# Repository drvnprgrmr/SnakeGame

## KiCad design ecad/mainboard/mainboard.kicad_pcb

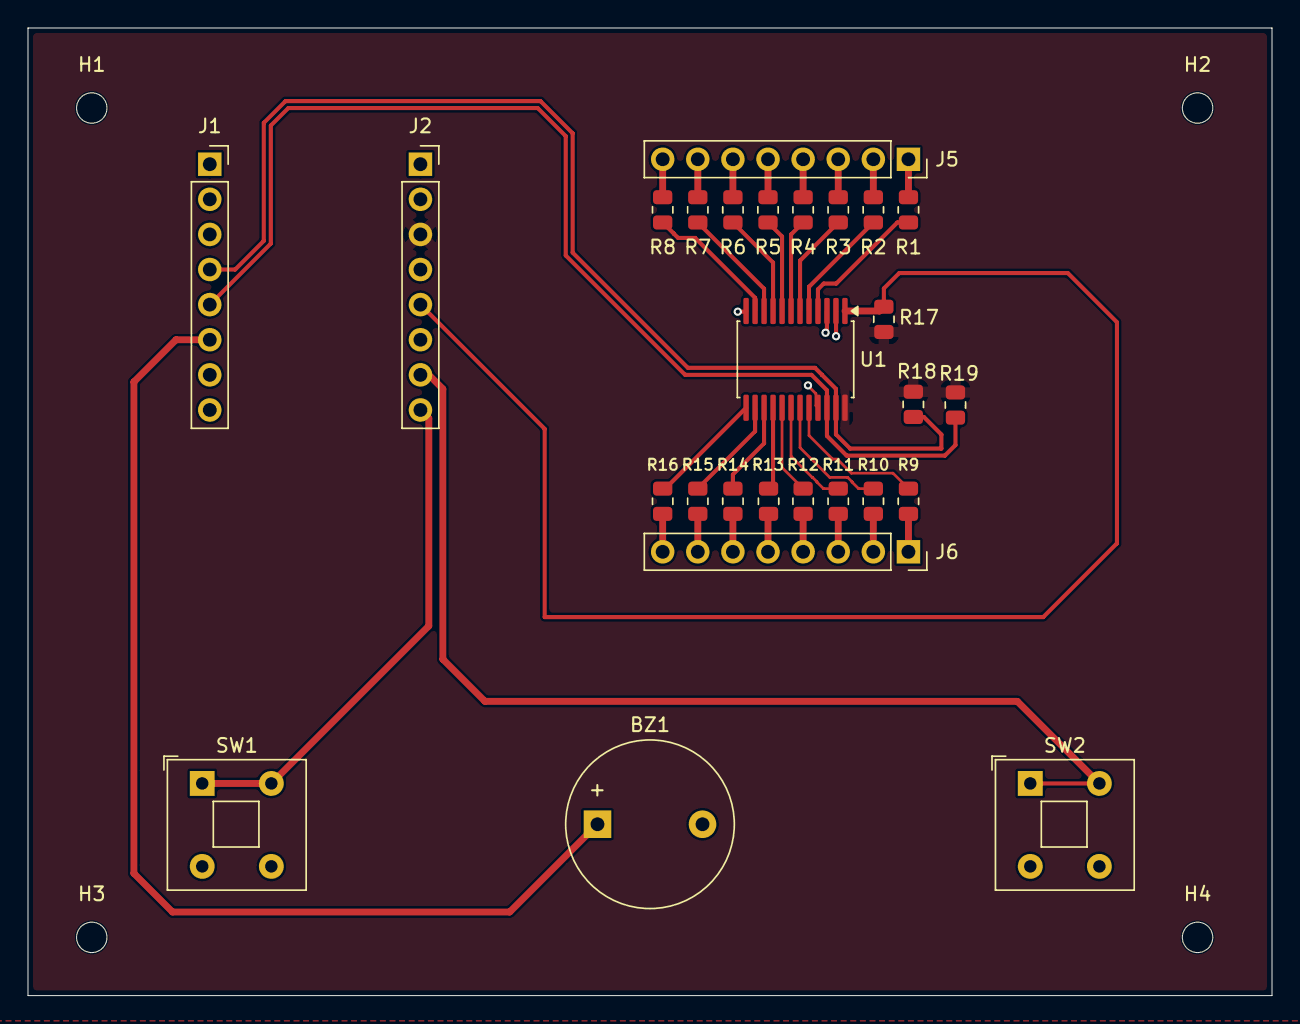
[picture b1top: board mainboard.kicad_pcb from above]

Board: 2 copper layers, 90.0 x 70.0 mm, 31 parts (0 on the bottom side), 40 nets.

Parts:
BZ1: Buzzer; Buzzer_12x9.5RM7.6
H1, H2, H3, H4: MountingHole; MountingHole_2.2mm_M2
J1: ESP32C3 Super Mini Left; PinSocket_1x08_P2.54mm_Vertical
J2: ESP32C3 Super Mini Right; PinSocket_1x08_P2.54mm_Vertical
J5: Dot Matrix Side A; PinSocket_1x08_P2.54mm_Vertical
J6: Dot Matrix Side B; PinSocket_1x08_P2.54mm_Vertical
R1, R2, R3, R4, R5, R6, R7, R8, R9, R10, R11, R12, R13, R14, R15, R16: 150; R_0805_2012Metric
R17: 10k; R_0805_2012Metric
R18, R19: 4.7k; R_0805_2012Metric
SW1: Left Button; SW_Push_2P1T_Toggle_CK_PVA1xxH1xxxxxxV2
SW2: Right Button; SW_Push_2P1T_Toggle_CK_PVA1xxH1xxxxxxV2
U1: PCF8575DBR; SSOP-24_5.3x8.2mm_P0.65mm

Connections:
+3.3V: J2.3, R17.1, R18.1, R19.1, U1.24 (VCC)
/BUZZ: BZ1.1 (+), J1.6
/DM_A1: J5.1, R1.1
/DM_A2: J5.2, R2.1
/DM_A3: J5.3, R3.1
/DM_A4: J5.4, R4.1
/DM_A5: J5.5, R5.1
/DM_A6: J5.6, R6.1
/DM_A7: J5.7, R7.1
/DM_A8: J5.8, R8.1
/DM_B1: J6.1, R9.1
/DM_B2: J6.2, R10.1
/DM_B3: J6.3, R11.1
/DM_B4: J6.4, R12.1
/DM_B5: J6.5, R13.1
/DM_B6: J6.6, R14.1
/DM_B7: J6.7, R15.1
/DM_B8: J6.8, R16.1
/LEFT_BTN: J2.8, SW1.1, SW1.2
/P0: R1.2, U1.4 (P0)
/P1: R2.2, U1.5 (P1)
/P2: R3.2, U1.6 (P2)
/P3: R4.2, U1.7 (P3)
/P4: R5.2, U1.8 (P4)
/P5: R6.2, U1.9 (P5)
/P6: R7.2, U1.10 (P6)
/P7: R8.2, U1.11 (P7)
/P10: R16.2, U1.13 (P10)
/P11: R15.2, U1.14 (P11)
/P12: R14.2, U1.15 (P12)
/P13: R13.2, U1.16 (P13)
/P14: R12.2, U1.17 (P14)
/P15: R11.2, U1.18 (P15)
/P16: R10.2, U1.19 (P16)
/P17: R9.2, U1.20 (P17)
/RIGHT_BTN: J2.7, SW2.1, SW2.2
/SCL: J1.5, R19.2, U1.22 (SCL)
/SDA: J1.4, R18.2, U1.23 (SDA)
/~INT: J2.5, R17.2, U1.1 (~INT)
GND: BZ1.2 (-), J2.2, SW1.3 (K), SW1.4 (A), SW2.3 (K), SW2.4 (A), U1.2 (A1), U1.3 (A2), U1.12 (GND), U1.21 (A0)

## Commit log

2026-04-16 initial commit
    setup esp-idf
2026-04-16 add dot_matrix module for interfacing with the dot matrix
2026-04-16 configure all row and column pins
    add readme and put description of working of the matrix
2026-04-16 add function to display init sequence for testing addressing
2026-04-17 add helper functions for multiplexing
2026-04-17 add license
2026-04-17 last commit with old logic
2026-04-17 load screen not working and watchdog being triggered
2026-04-17 almost fixed loadscreen
2026-04-17 fix display issues by implementing row by row scanning and adding sleep delay in the microseconds
    should be able to get them brighter by using lower LEDs (maybe 810ohms)
2026-04-17 fix load screen
2026-04-18 implement logic for moving snake
2026-04-18 draw snake and update in all 4 directions
2026-04-18 setup wifi softap
2026-04-18 fix logic of snake motion
2026-04-18 working on captive portal with issues
2026-04-19 get captive portal page working and redirecting
    yaato!
2026-04-19 add route for posting data and update web page to send json
2026-04-19 receive the data sent from queue
    really don't know what was wrong before
2026-04-19 get and store values from nvs
2026-04-20 setup dns forced captive and working on sta restart mode
2026-04-20 implement captive mode with couple of compile bugs
    will hopefully fix all current bugs in the next commit
2026-04-20 get the init sequence working
2026-04-20 minor cleanup
2026-04-20 add functionality for game control
2026-04-20 implement handlers for client sent control logic
2026-04-21 index row and col pins from all pins to avoid changing in two places
2026-04-22 implement food logic
2026-04-22 add game win and game lose logic
2026-04-22 add mdns service so as not to worry about ip addresses
2026-04-22 set custom hostname
2026-04-24 make dot matrix lib a .c file instead
2026-04-24 add pwm library
2026-04-27 buzzer working
2026-04-28 playing melody doesn't really work
2026-04-28 switch to blocking logic for playing melody but everything else freezes
2026-04-28 make buzzer to run in its own task
    fixes pause after playing tune in previous commit
2026-05-12 start working on schematics for the project
2026-05-12 complete schematics for v1 of board
2026-05-13 update footprints for the schematic
2026-05-13 begin placing components
2026-05-14 position dot matrix headers
2026-05-14 update pin headers for dot matrix
2026-05-14 place resistors for the dot matrix
2026-05-14 place io expander (pcf8575)
2026-05-14 remove extra pin headers for the dot matrix
2026-05-16 remove headers for io expander module and route tracks for the dot matrix
2026-05-16 add edge cuts to board
2026-05-16 place switches and buzzer
2026-05-16 resize and reposition edge cuts
2026-05-16 route all components and pass drc
2026-05-16 add text to back silkscreen and mounting holes
